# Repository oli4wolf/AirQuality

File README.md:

# AirQuality
Quick project to break my habit to remind me to open the window.

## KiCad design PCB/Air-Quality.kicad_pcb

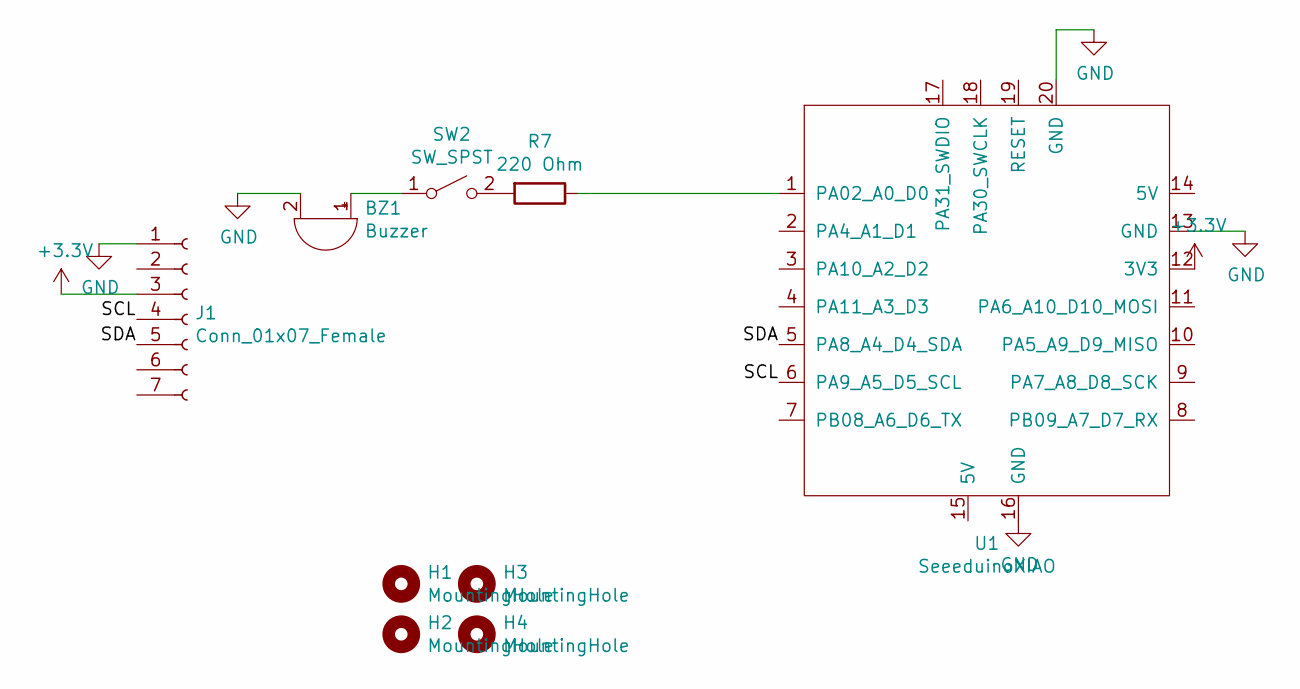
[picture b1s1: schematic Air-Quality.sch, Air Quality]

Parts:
BZ1: Buzzer; PUIAudio_SMT_0825_S_4_R
H1, H2, H3, H4: MountingHole; MountingHole_2.7mm_M2.5_ISO14580
J1: Conn_01x07_Female; PinSocket_1x07_P2.54mm_Vertical
R7: 220 Ohm; R_0805_2012Metric
SW2: SW_SPST; SW_DIP_SPSTx01_Slide_9.78x4.72mm_W7.62mm_P2.54mm
U1: SeeeduinoXIAO; Seeeduino XIAO-MOUDLE14P-2.54-21X17.8MM

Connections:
+3V3: J1.3, U1.12 (3V3)
/SCL: J1.4, U1.6 (PA9_A5_D5_SCL)
/SDA: J1.5, U1.5 (PA8_A4_D4_SDA)
GND: BZ1.2 (+), J1.1, U1.13 (GND), U1.16 (GND), U1.20 (GND)
unnamed: BZ1.1 (-), SW2.1 (A)
unnamed: R7.1, U1.1 (PA02_A0_D0)
unnamed: R7.2, SW2.2 (B)

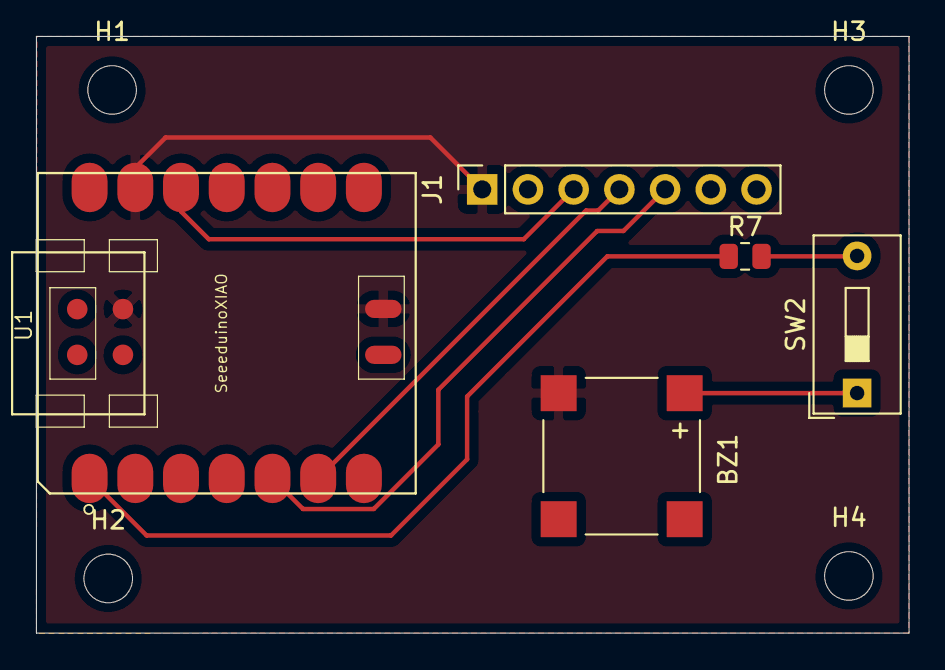
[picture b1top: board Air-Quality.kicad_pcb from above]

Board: 2 copper layers, 48.5 x 33.1 mm, 9 parts (0 on the bottom side), 7 nets.

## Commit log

2021-02-24 * Initial PCB Design
2021-03-02 * Initial working Arduino code without RTC DS3231 part.
2021-04-18 changed to RP 2040.
2021-05-05 Small Buzzer. Wrong Sensor Configuration :-(
2021-07-25 Version 3 for friends.
    Seeeduino
    New Sensor
2021-08-12 Update for the Trigger Value.
